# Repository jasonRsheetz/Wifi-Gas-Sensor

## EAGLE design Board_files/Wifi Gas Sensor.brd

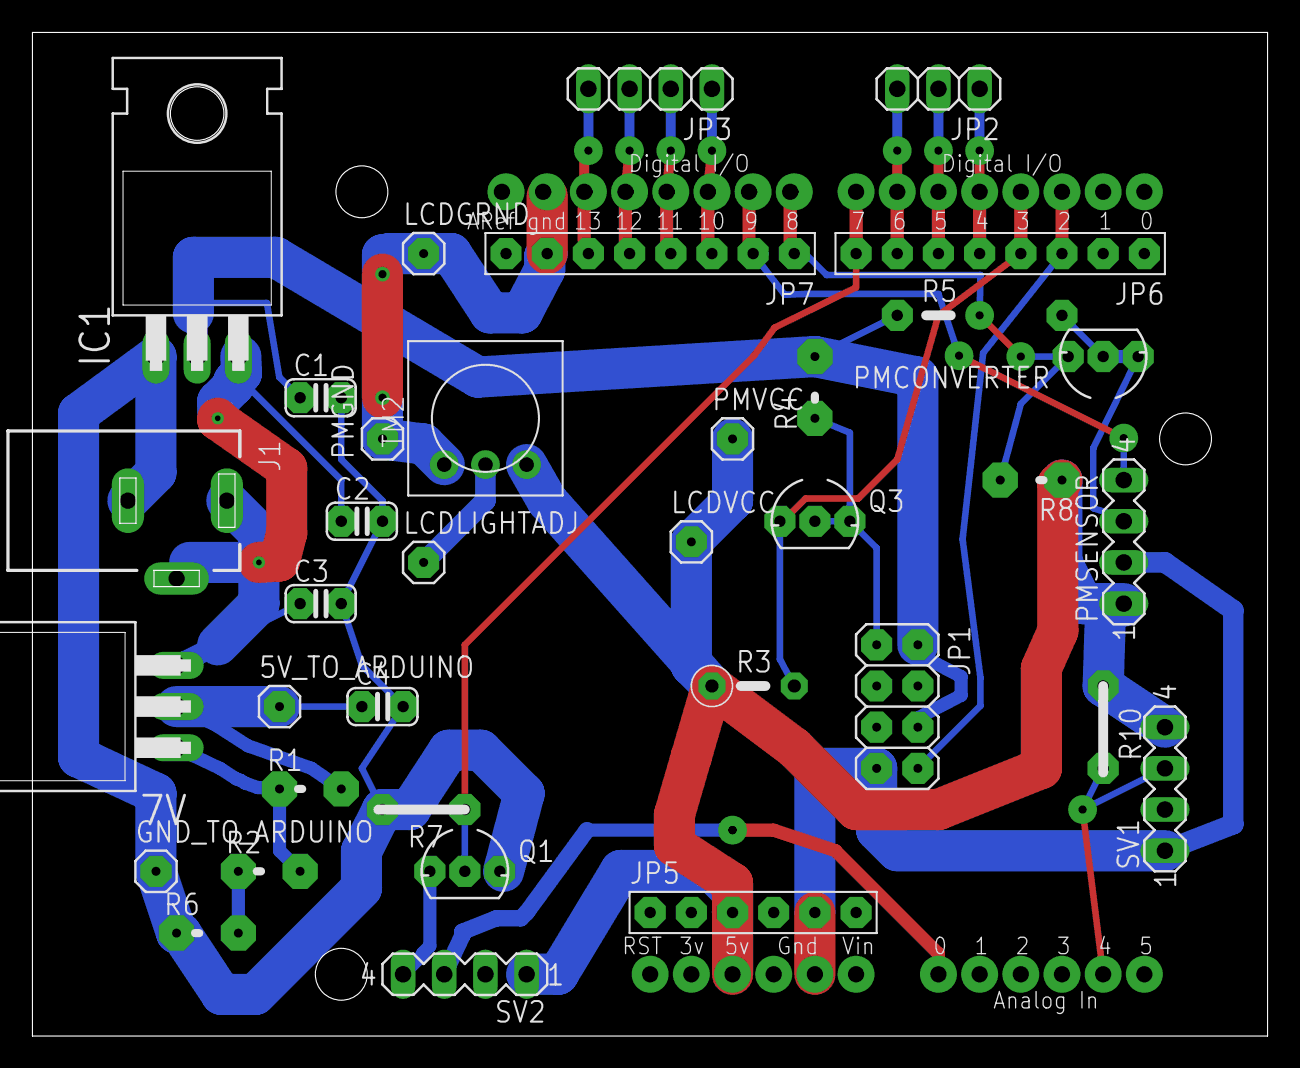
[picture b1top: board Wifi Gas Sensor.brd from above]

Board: 2 copper layers, 76.2 x 61.9 mm, 37 parts (0 on the bottom side), 33 nets.

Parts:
5V_TO_ARDUINO: 1X01
7V: 317T; TO220H
C1, C2, C3, C4: C025-024X044
GND_TO_ARDUINO: 1X01
IC1: 7805T; TO220H
J1: DCJ0202
JP1: 2X04
JP2: 1X03
JP3: 1X04
JP5: 1X06-BIG
JP6, JP7: 1X08-BIG
LCDGRND: 1X01
LCDLIGHTADJ: 1X01
LCDVCC: 1X01
PMCONVERTER: FQN1N50CI; TO92-INLINE
PMGND: 1X01
PMSENSOR: MA04-1
PMVCC: 1X01
Q1, Q3: FQN1N50CI; TO92-INLINE
R1, R2, R4, R6, R8: 0204V
R3, R5: 0207/5V
R7, R10: 0207/2V
SV1, SV2: MA04-1
TM2: TRIM-3386
U$2: ADAFRUITUSER_ARDUINO-BPLACE

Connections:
GND_TO_ARDUINO: C1.2, C2.2, C3.2, C4.2, GND_TO_ARDUINO.1, IC1.1, J1.3, Q1.3, R6.1, R7.2
unnamed: 5V_TO_ARDUINO.1, 7V.2, C4.1, R1.2
unnamed: 7V.1, R1.1, R2.2
unnamed: JP2.1, JP6.5, U$2.D4
unnamed: JP7.2, PMSENSOR.4, U$2.D9
unnamed: JP6.4, Q3.1, R3.2, U$2.D3
unnamed: JP2.2, JP6.6, U$2.D5
unnamed: JP2.3, JP6.7, U$2.D6
unnamed: JP3.4, JP7.6, U$2.D13
unnamed: JP3.3, JP7.5, U$2.D12
unnamed: JP3.2, JP7.4, U$2.D11
unnamed: JP3.1, JP7.3, U$2.D10
unnamed: SV2.3, U$2.A0
unnamed: Q1.1, SV2.4
unnamed: JP5.4, U$2.GND2
unnamed: JP7.1, PMCONVERTER.3, R8.2, U$2.D8
unnamed: JP1.7, JP5.5, PMSENSOR.2, SV1.1, U$2.GND1
unnamed: R2.1, R6.2
unnamed: 7V.3, C2.1, C3.1, IC1.3, J1.1
unnamed: JP6.8, Q1.2, R7.1, U$2.D7
unnamed: JP5.3, LCDVCC.1, PMSENSOR.1, PMVCC.1, R3.1, R8.1, R10.1, SV1.4, SV2.1, TM2.3, U$2.5V
unnamed: JP5.6, U$2.VIN
unnamed: JP1.8, JP6.3, U$2.D2
unnamed: C1.1, IC1.2, JP1.2, JP1.6, R4.2, R5.1
unnamed: JP5.2, U$2.3V
unnamed: JP5.1, U$2.RESET
unnamed: JP6.1, U$2.D0
unnamed: JP6.2, U$2.D1
unnamed: JP7.7, LCDGRND.1, PMGND.1, TM2.1, U$2.GND
unnamed: LCDLIGHTADJ.1, TM2.2
unnamed: R10.2, SV1.3, U$2.A4
unnamed: JP1.1, Q3.2, Q3.3, R4.1
unnamed: PMCONVERTER.1, PMCONVERTER.2, PMSENSOR.3, R5.2

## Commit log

2018-05-05 "adding .ino files, esp flashing tool and command documentation
2018-05-05 begin writing code to upload multiple data entries
2018-05-06 update .ino to include a scheme to upload each data field at 15 second intervals, this scheme is untested at this point
2018-05-07 redesigned board file pdf's for printing
2018-05-11 increased the diameter of some vias, and decreased the drill size
2018-05-11 increased size of vias and pin headers
2018-05-11 new pdf file to print with larger vias and pin headers
2018-05-11 increased pin header size again
2018-05-12 corrected barrel jack routing
2018-05-12 working program, needs to only be cleaned up and commented
